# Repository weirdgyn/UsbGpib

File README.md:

# Table of contents

:newspaper: [Latest updates](Updates.md)
<br> :hammer: [Buy it or build it](#buy-it-or-build-it)
<br> :wave: [UsbGpib Introduction](#usbgpib-introduction)
<br> :house: [Housing / Enclosure](#housings)
<br> :computer: [Software](#software)
<br> &nbsp; &nbsp; :electric_plug: [Using the device](#using-the-device)
<br> &nbsp; &nbsp; :gear: [Setting and getting parameters](#setting-parameters)
<br> :heavy_check_mark: [Testing status](#testing-status)
<br> :notebook: [Tutorials](Tutorials/README.md) <- **New!**
<br> :heart: [Support the Project](#support-the-project)

# Summarized latest updates

For detailed visibility look under the Latest update link above!

[17h Aug 2026] Nice project: **[XyphroLabs-USBGpib-DMM4050](https://github.com/ZandanKhan/XyphroLabs-USBGpib-DMM4050)** — a Python GUI by [Zandan Khan](https://github.com/ZandanKhan) for controlling the Tektronix DMM 4050 (6½-digit precision multimeter) over UsbGpib, with measurement logging to CSV. Great example of building a full front-end on top of this adapter.

[17th Aug 2026]: **GPIBee is available, but...**

# GPIBee = UsbGpib V3 is available!

The title says it: GPIBee - UsbGpib V3 - is now available. Finally!  
  
It's for everyone who's told me, in issues and DMs, "I love this, but I don't have time to build one": USB-C and Ethernet with PoE, VXI-11 with multiple simultaneous sessions, and 3.5-5x the speed of V2 - in a proper enclosure, with real support behind it. 
It's built, tested, and shipping now.

I put together a short video showing it in action: [Introducing GPIBee](https://lnkd.in/epR7Xf-b).  
And you can find the full details at [GPIBee.com](https://www.gpibee.com).

This didn't come out of nowhere - there's a bit of a story behind it, including one thing I haven't said outright until now, something I went back and forth on for quite a while before deciding.

~7 years ago I started UsbGpib as a weekend project: An open, MIT-licensed way to talk to GPIB instruments without paying for an $800+ commercial adapter. I never expected it to pick up 642 stars, 82 forks, and end up soldered into home labs, universities, and repair benches around the world. That still means a lot to me, and it's the reason I kept and keep maintaining it for as long as I have.

A fair bit of that maintenance happened on evenings and weekends that would otherwise have gone to family time or just switching off. Nothing dramatic - just the normal trade-off of a side project that grew bigger than expected. Honestly, the part I'll remember most isn't the hours, it's the people: The issues, the emails, the odd late-night message or calls from someone debugging their own build. I've genuinely enjoyed those conversations, and they're a big part of why I kept going.

Along the way I also learned some harder lessons. To be clear, I've always been and are genuinely happy to see people or companies build their own UsbGpib - that's exactly what open source is for. What sat less well with me was seeing unrelated manufacturers turn V2 into a business of their own, selling it at scale with no attribution back to the project. That's a different thing entirely from working with official partners like Elecrow and Binho, who I have a real relationship with and who've supported this project properly.

But it stayed with me while I was figuring out what V3 should be, and it wasn't an easy decision to make.

So here's the thing I haven't said outright until now: V3 - GPIBee - is a commercial product rather than an open one. Something which might change in future, but for now it is.

That's a real change from V1/V2, and I don't want to gloss over it.

Here's the honest reasoning:

- Going commercial means there's a sustainable way to keep this going, rather than relying on whatever spare evenings I happen to have.
- It lets me fund the things a hobby project can't - CNC-machined, EMI-shielded enclosures, firmware QA, and proper support.
- It gives the project a legitimate path forward that undercutting clones can't quietly erase.

None of that changes what's already yours. V1 and V2 stay exactly as they are - MIT-licensed, fully open, schematics and firmware included, free to build and modify. And to be clear: I'm not walking away from it. I'll keep maintaining UsbGpib - answering issues, keeping it working - alongside GPIBee, not instead of it.

I'm proud of where this landed, and I'm looking forward to keeping both projects going - UsbGpib and GPIBee side by side. Thanks for seven years of bug reports and good conversations so far, with plenty more to come I hope. I hope some of you will give GPIBee a look, and either way, I'd genuinely love to hear what you think.

---

# Buy it or build it

* Tired of tinkering? Want to skip the hassle and get straight to using your GPIB setup?  
* You’d rather spend your time using your instruments instead of assembling hardware?

Skip the soldering iron and jump straight into your GPIB workflow!

You’ve got two solid options to get a ready‑to‑run UsbGpib adapter.

## &#x1f1fa;&#x1f1f8; - United States
* If you're in the US, you can now order the UsbGpibV2 directly from several sources, including my distribution partner Binho LLC. Enjoy fast domestic shipping with no long waits, no customs paperwork, and no surprises - just quick delivery and a smooth experience: 
<br> &#x1F449; <a href="https://binho.io/test-measurement/products/usbgpib-v2/" target="_blank">https://binho.io/test-measurement/products/usbgpib-v2/</a>
<br> &#x1F449; <a href="https://www.digikey.com/short/29nqq5cz" target="_blank"> https://www.digikey.com/short/29nqq5cz</a>
<br> &#x1F449; Amazon US also has it listed, but right now no stock, but worthwhile to check it out there too.

## &#x1F30E; - Worldwide
* I’ve teamed up with Elecrow to bring you ready-to-roll GPIB-USB converters – perfect for those who want results, not a weekend project.
* These adapters come fully assembled, programmed, housed, tested, and ready to go. No fuss. No build. Just plug it in and start working.
* The Adapters match 100% the V2 version described in this repository. 
* &#x1F449; <a href="https://www.elecrow.com/xyphrolabs-gpibusb.html" target="_blank">https://www.elecrow.com/xyphrolabs-gpibusb.html</a>

Let the data flow begin!

This doesn’t mean I’m going fully commercial - far from it.
Offering pre-built adapters is simply a convenience for those who’d rather skip the build and get straight to using their gear.

All sharing, support, and collaboration will remain fully open, just as before.
This is about choice, not change!

The full design files are located in this repository in case you want to build the devices yourself.

---

# UsbGpib Introduction
Versatile, cheap, portable and robust USB to GPIB converter (USBTMC class based).

You'll find many projects like this, but this one is special (ok, everybody will claim this) :-)

V1 Hardware: 

V2 Hardware: 

If you have a lot of test equipment at home, you might know the issues: Lots of devices only have GPIB as interface and the GPIB adapters and GPIB cables on the market are very expensive and some of them even have many issues, when run under Windows 10 (device driver does not work). Or they e.g. are not able to be operated with VISA, because they are UART based, need special command sequences, ...

The adapters are also typically very long, such that they extend the overall length of your test equipment by at least 10cm (~4 inches).

Apart of the 2 very big manufacturers, other GPIB adapters, e.g. with Ethernet or also USB interface are not recognized by normal VISA providers or PyVisa, making the measurement control implementation specific for your GPIB adapter.

I've got frustrated and tried to turn it into something positive. Here a video showing the final device in action - click to view:

Some goals of the project were:
- Work based on the standard USBTMC protocol. This allows the GPIB test equipment to look like a normal USB based measurement device and work flawless with e.g. NI VISA, Labview, Matlab or PyVisa.
- Have a small length - otherwise my equipment has the risk of falling from the shelf :-) Also the USB cable should connect 90 degree angled, to make it very short. With V2 HW, the length got further reduced to the size of a GPIB connector.
- It should be cheap but still versatile (you can build a single one of these for only 14 USD!)
- It should support ALL my test equipment, from many different GPIB implementation generations and different GPIB flavors
- The Firmware should be upgradeable over USB
- It should be rock-solid (!) I don't want to end up in a very long measurement being interrupted because of a software issue of my USB GPIB converter.
- It should support additional features like serial poll, remote enabling/disabling
- If there is no GPIB device connected to the USBGpib converter, or the GPIB device is powered down, there should be no USB device visible on the PC.

All those goals are met.

---

# Hardware

## Microcontroller choice

Although I typically would prefer nowadays an ARM Cortex M0/3/4/7 controller, there is an issue with it. Available devices support only max. 3.3V supply voltages, such that there would be a requirement for a level-shifter towards the GPIB Bus.
GPIB is based on 5V (not exactly true, but a first iteration).

This limited the microcontroller choice to e.g. AVR or PIC controllers. Because of very good availability I ended up in ATMEGA32U4 controllers.
Apart of the device supporting 5V I/O voltages, it also does not require a regulator to be part of the application - it has an internal 3.3V regulator. This minimizes the full application schematic and BOM.

Apart from that, there is an excellent USB stack available [http://www.fourwalledcubicle.com/LUFA.php](http://www.fourwalledcubicle.com/LUFA.php).

The GPIB side of the schematic can be directly connected to the ATMega32U4 IO pins. The IO pins from the microcontroller side are only set to 2 different states: Tri-state (input) or output LOW, to talk over GPIB.

## Component sourcing

All components are easy to source, so I only specify the potential critical ones:

- 16 MHz Crystal: Farnell 2853867 - MCSJK-7E-16.00-8-30-100-B-30 
- REV 1 GPIB connector: Farnell 2421095 - NORCOMP 112-024-113R001. For REV 2 use a straight 24P male solder type connector e.g. from AliExpress.
- USB connector for V1 HW: Farnell 2668483 - Amphenol ICC 61729-1011BLF
- USB connector for V2 HW: Best is to look on AliExpress for 57 series 24P connector as a starting point.

## PCB

The PCB can be ordered at nearly any PCB pool production service (e.g. 10 PCBs for 2 USD + shipping). The gerber files are included in the "HW/Gerber files" subdirectory.

## Mounting the PCB & Flashing the firmware

The PCB is available in 2 revisions.
- [REV 1](HW/REV1/README.md) is the most popularly used right now due to age. It has a USB Type-B connector and an L-shaped housing visible on a few photos of this page.
- [REV 2](HW/REV2/README.md) has some improvements like being smaller, better fit and USB Type-C connector.
- A REV 3 is upcoming. It will be a major redesign with more speed, Ethernet and power over Ethernet support, but the same DNA: Standard protocols being used and ensure compatibility and stability!

Choose whatever you prefer. The software images, but also the external behavior is the same.

---

# Housings

## REV 1

I created a sophisticated 3D printable housing for this adapter. The design was made with Fusion 360. The project file + the STL files are included in the "Housing" sub directory.

The PCB fits perfectly into it. Optionally it can be fixed with 2 mounting screws (the GPIB connector has 2 threads, use 2 times 4-40 UNC x 3/8) and the TOP cover snaps onto the housing base.

I printed this using an Ender 5 3D printer with black PLA, 0.15mm layer height, 1mm wall thickness, no support.
Take care, that you rotate the TOP part of the housing by 180 degrees, so that the flat side is located on the printer bed.
Printing works fine, several iterations of the design were made to ensure good printability.
I printed so far 15 housings, without a single fail.

More information on this REV 1 can be found here: [REV 1](HW/REV1/README.md).
Note, that also the programming/build instructions moved to this location.

## REV 2

The REV 2 housing is a lot smaller, but requires 2 screws.
The housing is quite important to be able to connect and disconnect the board without breaking anything. It is key for mechanical stability of the adapter.
When operating the device without housing, take very well care when plugging in and out the board in case the GPIB connector has a very tight fit.

Information on how to build it can be found in the HW/REV 2 folder: [REV 2](HW/REV2/README.md).
Note, that also the programming/build instructions moved to this location.

---

# Software

## Source code

The source code of the Boot loader (slightly modified LUFA MassStorage Boot loader) and the main USBGPIB converter are located in the "SW" subdirectory.
At the time of publication LUFA 170418 release was used, with GCC as compiler.

Note: The Software is compatible with any HW revision in this repository. For REV 1 and REV 2 hardware you don't need different SW images.

## Binaries

For those, that just want to create their own device, I've included the binary output in the "SW/binaries" subdirectory.

---

# Using the device

## USB enumeration

You might be surprised initially, that the device does not show up in your device manager (or lsusb), when you connect only the USB side. This is a feature, not a bug (really!).
Only, if a GPIB device is connected, you can see the device on your PC too.

The reason behind the feature is simple: Instead of having a standard GPIB wiring, where you have a single GPIB controller and lots of GPIB devices interconnected, USBGPIB supports only a direct connection of the USBGPIB device to your measurement device. If you have like me e.g. 14 Instruments you don't want all to show up in the device manager, if the measurement device itself is powered down - you won't anyway be able to communicate with a powered down device.

When USB and the GPIB side is connected, the device enumerates. The USBGPIB device reads out the ID of the instrument and constructs a unique USB Serial number out of it. It is thus easily possible to assiate multiple connected USBGPIB devices with the measurement instrument.

The VISA ressource name is constructed from this USB Serial number. You can identify easily e.g. in NiMax, which device is connected:

If you connect your USBGPIB device afterwards to another GPIB measurement device, it will disconnect and connect with a new serial number string, matching the other GPIB device *IDN? response again.

## GPIB settings on your measurement device

GPIBUSB does probe all GPIB primary addresses (and secondary address 0) for presence of a GPIB Talker/listener. It is thus not required to set a specific GPIB address - GPIBUSB will find it itself.

The only importance setting on the measurement device is, that the GPIB interface is enabled, which is typically the case.

## LED indicator

The LED indicates different states:

LED blinking: The USBGPIB converter is connected to a measurement instrument, it is powered off or its GPIB port is disabled. In this state, the device is also not connected to USB and will not show up in the device manager or lsusb.
LED on: The device is connected to a measurement device and GPIB communication possible. It is also accessible over USB
LED off: The device is not connected over USB, or the PC powered off :-)

## Controlling GPIB devices

As this converter implements the standard USBTMC Test and measurement class, you can control your instrument from ANY of the normal VISA tools. I tried so far R&S VISA and NI Visa, using Python and Matlab to talk to the devices.

# Testing status

This project is actively maintained since more than 6 years and I personally consider it as very stable. It is proven by multiple users to operate on MacOSX, Linux and Windows and measurement equipment from several decades.

In general I take bug reports very serious and want to "fix them all". In case you don't get an answer on-time on items you report in the issues section, please write me: Xyphro@gmail.com. 
I often miss seeing issue reports very quickly, as I don't get an email once they are filed.

## Sucessfully tested measurement equipment:

Below list is equipment I mainly myself tested. Many other users have other measurement equipment proven in use already.

- R&S FSEM30
- R&S SMIQ03
- R&S CMU200
- R&S SMW200A
- R&S FSW
- R&S FSV
- Keithley 199 multimeter
- HP 34401 DMM from different generations / with different FW versions
- HP 3325A synthesizer/frequency generator
- HP 3457A multimeter
- Agilent E4406A VSA transmitter tester
- Tektronix TDS7104 Digital Phosphor Oscilloscope
- HP 8596A spectrum analyzer
- Agilent E3648A dual power supply

A rather incomplete summary of equipment reported to work from users is:
- Keithley S46T
- HP/Agilent/Keysight 34401A of different generations
- HP/Aglient/Keysight 34410A
- Agilent N6700B
- Agilent E4416A
- Agilent 34970
- Keysight E3645A
- Keithley 2230G-30-1
- Keithley 2601A
- Tektronix AFG3102
- Tektronix 3014C
- Rohde & Schwarz SMB 100A
- Agilent E3631A
- ICS 4899GPIB
- TTI QL564TP
- Lecroy LW110
- LeCroy 334A
- LeCroy 354A
- Hameg 3524
- Fluke 5522A
- Fluke 5500A 
- and many more... It will take quite a while till I have parsed all my emails for working instruments :-)

## Scenarious

- It works under all popular operating systems like Windows 7 and 10, 11, Linux and MacOSX
- USB1.1, USB2.0 and USB3.x ports tested, with and without USB HUB in between.
- The connection stays responsive, when power cycling the PC, or hibernating/sleeping it
- Different connection cycles (GPIB side connected first, USB side connected first, swapping GPIB side equipment, ...)
- Extensive testing of timeout scenarious. E.g. making an illegal query and testing, if the USBTMC handles the timeouts properly. This was a very tricky part to get right.
- Tested special transfer modes. E.g. capturing screenshots from different equipment is usually something, which will drive other GPIB adapters to the limits, because binary data of unknown length needs to be transported successfully.

# Setting Parameters

The firmware version from 13th January 2024 onwards has the ability for human readable text base configuration of several parameters.
The previous methods are still supported, but won't be further documented. You can look them back in the history of this file.

The command parser is quite simple. For that reason follow the exact syntax as shown below. 
Don't add extra spaces or make other modifications or concatenate commands.

## Read termination method

While most GPIB interfaces use the hardware signal EOI to signal the end of a message, not all old equipment supports it. Some older instruments even don't have the EOI pin hardware wise wired and use \r or \n termination.

The USB-TMC standard allows to set the read termination. While in firmware versions before < 2.0 I did not enable that method, it is now finally supported with standard compliance.

I document here the older method (using pulse indicator request), but I add also the newer methods which are 100% UsbTmc compliant and portable across different equipments. You can choose which ones to use, but in some cases pulse indicator requests can be difficult to issue, for which reason it is likely better to use the standard compliant method.

### Set read termination to CR (\r):
(old method)
```
dev.control_in(0xa1, 0x40, 0, 0, 1); # USBTMC pulse indicator request (enables internal command processing)
dev.write('!term cr')
```
Above setting is volatile. To make this a permanent setting call the below mentioned "!term store" command.

(prefered method) Alternatively you can set the termination directly with visa means, e.g. using PyVisa:
```
dev.set_visa_attribute(visa.constants.VI_ATTR_TERMCHAR_EN, True)
dev.set_visa_attribute(visa.constants.VI_ATTR_TERMCHAR, ord('\r') )
```

### Set read termination to LF (\n):
(old method)
```
dev.control_in(0xa1, 0x40, 0, 0, 1); # USBTMC pulse indicator request (enables internal command processing)
dev.write('!term lf')
```
Above setting is volatile. To make this a permanent setting call the below mentioned "!term store" command.

(prefered method) Alternatively you can set the termination directly with visa means, e.g. using PyVisa:
```
dev.set_visa_attribute(visa.constants.VI_ATTR_TERMCHAR_EN, True)
dev.set_visa_attribute(visa.constants.VI_ATTR_TERMCHAR, ord('\n') )
```

### Set read termination to EOI only (default setting):
(old method) 
```
dev.control_in(0xa1, 0x40, 0, 0, 1); # USBTMC pulse indicator request (enables internal command processing)
dev.write('!term eoi')
```
Above setting is volatile. To make this a permanent setting call the below mentioned "!term store" command.

(prefered method) Alternatively you can set the termination directly with visa means, e.g. using PyVisa:
```
dev.set_visa_attribute(visa.constants.VI_ATTR_TERMCHAR_EN, False)
dev.set_visa_attribute(visa.constants.VI_ATTR_TERMCHAR, ord('\0') )
```

### Save readtermination setting in eeprom (make them non-volatile)
```
dev.control_in(0xa1, 0x40, 0, 0, 1); # USBTMC pulse indicator request (enables internal command processing)
dev.write('!term store')
```

Above relates to the "old non prefered method". In general it is a good idea to set the read termination volatile and use the above suggested methods highlighted with (prefered method).

### Query current termination setting from device
```
dev.control_in(0xa1, 0x40, 0, 0, 1); # USBTMC pulse indicator request (enables internal command processing)
print(dev.query('!term?'))
```
This returns a text string containing "lf", "cr" or "eoi"

## Multi-device support - Setting the GPIB device target address

Since Firmware version V2.4 USBGpib allows supporting multiple instruments.

While the USBTMC protocol allows only setting a single device to be addressed and composite USB devices are not well supported by all VISA implementations, I decided to add a command to set the address of the GPIB device which is addressed.

There is a minor limitation of this approach, which is that service request SRQ handling is only done properly to the currently selected GPIB device.
Another one is, that users shall never forget to set the GPIB address to the correct setting before issuing a command.

### Setting a primary address only

Substitute the text <Primary_address> with a number from 1 to 30 to set the primary address of the new GPIB device to talk to in following GPIB transactions

```
dev.control_in(0xa1, 0x40, 0, 0, 1);
dev.write('!addr <Primary_address>')
```

### Setting a primary + secondary address

Substitute the text <Primary_address> with a number from 1 to 30 to set the primary address and <Secondary_address> with a number from 0..6 or 96..102 of the new GPIB device to talk to in following GPIB transactions.
Note, that not the full subaddress range of 0..31 or 96..127 is supported as of now - this requires a bit more work. Most common device with subaddresses like R&S CMU200 only are well covered with that current range.

```
dev.control_in(0xa1, 0x40, 0, 0, 1);
dev.write('!addr <Primary_address> <Secondary_address>')
```
### Python wrapper example code for GPIB address setting

```
import pyvisa as visa
dev = 'USB0::0x03EB::0x2065::GPIB_22_14236333938351C00011::INSTR'
rm = visa.ResourceManager()
dev = rm.open_resource(dev, open_timeout=1000)

def set_gpib_addr(primary_address, secondary_address = None):
    dev.control_in(0xa1, 0x40, 0, 0, 1);
    if secondary_address is None:
        dev.write('!addr %d' % primary_address);
    else:
        dev.write('!addr %d %d' % (primary_address, secondary_address));
    
# Address CMU200, which is for me on primary address 1, secondary address 0
set_gpib_addr(1, 0)
print(dev.query('*IDN?'))

# address HP3457A on primary GPIB address 22
set_gpib_addr(22)
dev.write('END,ALWAYS')
print(dev.query('ID?'))
```

This code results in my current testsetup with CMU200 and HP3457A in this output:

```
Rohde&Schwarz,CMU 200-1100.0008.02,xxxxxx,V5.22

HP3457A
```

## AutoID setting

Default wise the GPIB adapter tries during power on of the instrument to query using *IDN? or ID? commands the instrument name automatically.
This is used to build the USB serial number, which finally gets part of the VISA ressource string.

Not all instruments support this *IDN / ID? query. For this reason this feature can be turned off.
The serial number will then be built based on the GPIB address of the instrument.

### Turn AutoID feature off
```
dev.control_in(0xa1, 0x40, 0, 0, 1); # USBTMC pulse indicator request (enables internal command processing)
dev.write('!autoid off')
```
This setting is stored in eeprom = non volatile memory, so will survive a power cycle

### Turn AutoID feature on
```
dev.control_in(0xa1, 0x40, 0, 0, 1); # USBTMC pulse indicator request (enables internal command processing)
dev.write('!autoid on')
```
This setting is stored in eeprom = non volatile memory, so will survive a power cycle

### turn auto ID on with delay

Some instruments need after turn on some seconds before GPIB is responsive.

With below 3 settings you can set a delay which is applied before the instrument ID is queried after power on.
Note that it will take then also more time, before the USB device is recognized by the PC.

Also this setting is non-volatile.

Delay 5 seconds:
```
dev.control_in(0xa1, 0x40, 0, 0, 1); # USBTMC pulse indicator request (enables internal command processing)
dev.write('!autoid slow')
```

Delay 15 seconds:
```
dev.control_in(0xa1, 0x40, 0, 0, 1); # USBTMC pulse indicator request (enables internal command processing)
dev.write('!autoid slower')
```

Delay 30 seconds:
```
dev.control_in(0xa1, 0x40, 0, 0, 1); # USBTMC pulse indicator request (enables internal command processing)
dev.write('!autoid slowest')
```

### read autoid setting

```
dev.control_in(0xa1, 0x40, 0, 0, 1); # 
print(dev.query('!autoid?'))
```
Returns as text string either: "off", "on", "slow", "slower" or "slowest".

## Firmware version

Finally I implemented a command to query the USB adapters firmware version :-)

```
dev.control_in(0xa1, 0x40, 0, 0, 1); # USBTMC pulse indicator request (enables internal command processing)
print(dev.query('!ver?'))
```

## Shorten ressource strings (Matlab)

A user discovered that Matlab has a limitation in the VISA ressource string length and shared a pull request to reduce the length.
I expose this now first time in the baseline firmware with the following options.

This setting is stored in eeprom = non volatile.

### Limit the USB serial number to a length of 20 characters
```
dev.control_in(0xa1, 0x40, 0, 0, 1); # USBTMC pulse indicator request (enables internal command processing)
dev.write('!string short')
```

### disable limitation of USB serial number length (default behavior)
```
dev.control_in(0xa1, 0x40, 0, 0, 1); # USBTMC pulse indicator request (enables internal command processing)
dev.write('!string normal')
```

### query the string length setting.
```
dev.control_in(0xa1, 0x40, 0, 0, 1); # USBTMC pulse indicator request (enables internal command processing)
print(dev.query('!string?'))
```

This returns as text string either "normal" or "short".

## reset the adapter
```
dev.control_in(0xa1, 0x40, 0, 0, 1); 
dev.write('!reset')
```

Do a reset of the adapter. Note that due to the reset you have to close the visa session and start a new one as the device re-enumerates on the USB.

---

# Support the project

Or support by buying a fully prebuilt adapter at: <a href="https://www.elecrow.com/xyphrolabs-gpibusb.html" target="_blank">https://www.elecrow.com/xyphrolabs-gpibusb.html</a>

In general any email, post or feedback is also very valuable, and don't feel bad if you don't use the support options :-)
Feel free to contact me at Xyphro@gmail.com

---

This page is from XyphroLabs UsbGpib project: <a href="https://github.com/xyphro/UsbGpib" target="_blank">https://github.com/xyphro/UsbGpib</a>

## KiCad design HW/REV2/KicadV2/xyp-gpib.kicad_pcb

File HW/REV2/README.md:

# xyphro UsbGpib HW REV 2

The new HW revision picks up some things that I and other misliked:
- The REV 1 HW - when put beeing assembled into its housing did have change to colide with parts of the instruments body. Especially for Keysight equipment. This new HW revision follows the formfactor of an original GPIB cable to get rid of this mechanical constraint.
- The REV 1 HW required to enter the bootloader with a tweezer. REV 2 has a button. Hold it a few seconds and the bootloader is entered.

The [software](../../SW) will always stay the same, no matter if REV1 or REV 2.

I have built many of those adapters myself so far and have developed trust in the design:

## Assembly process

All files related to HW are located in this folder. Gerber file, BOM, Kicad design files.

## preparing the PCB

Mount only the SMD components. This means: DON'T mount the GPIB connector yet.

On edge you can find a mounting point for a pinheader - 45 degrees angled. Mount 2-3 pin pinheaders here and you now have a 6 pin ISP programming port with standard pinout for your favorit AVR programmer.
Program the bootloader. Pin 1 is marked on the PCB to allow you connecting the ISP cable in the correct orientation.

### Flashing the Microcontroller first time

For initial programming an AVR ISP adapter is needed to program the "Bootloader.hex" file.

It is very important, that the Fuses of the AVR are programmed.

Here an example how to program the bootloader using avrdude (using usbasp programmer):
```
avrdude -c usbasp -p m32u4 -e -Ulock:w:0xFF:m -Uefuse:w:0xcb:m -Uhfuse:w:0xd8:m -Ulfuse:w:0xde:m
avrdude -c usbasp -p m32u4 -U flash:w:BootLoader.hex
```
To program bootloader and application image at the same time using AvrDude, you can use this command:
```
avrdude -c usbasp -p m32u4 -e -Ulock:w:0x3F:m -Uefuse:w:0xcb:m -Uhfuse:w:0xd8:m -Ulfuse:w:0xde:m -U flash:w:TestAndMeasurement.hex -U flash:w:BootLoader.hex
```
Note, that some programmers use a quite high clock frequency on the programming interface. In case of failures try to decrease the SCK clock frequency!

After programming the file, disconnect and connect the device and a USB drive will show up. Copy the TestAndMeasurement.bin file to this USB drive - ideally using the command line. Example: `copy TestAndMeasurement.bin F:\FLASH.BIN`.
On Linux, there is a bug with the LUFA mass storage that means it is required to use `dd if=TestAndMeasurement.bin of=/mnt/FLASH.BIN bs=512 conv=notrunc oflag=direct,sync`.

When done, disconnect USB.

It is now safe to desolder the ISP pinheaders such that the PCB fits into the housing. 
Any further update can happen over USB using the bootloader.

## Building the whole thing together
Preparation:
- Mount the PCB EXCLUDING the GPIB connector.
- Print the housings located in [this folder](../../Housing/Rev2). I print them using 1mm bottom/top/wall thickness, 0.16mm layer height and 30% infil. On my K1 printer it takes 23 minutes to print, on my Ender 5 2.2 hours.
- get 2 20mm M3 screws and 2 M3 nuts
- get a GPIB connector "24P Male solder type" from e.g. Aliexpress

If you have everything in place and prepared, insert the PCB including the GPIB connector (unsoldered!) into the bigger part of the housing:

Then solder 2 pins of the GPIB connector and take the PCB out of the housing again to solder all pins.
(This step is required to ensure that the GPIB connector has the right distance to the PCB and fit into the housing)

As a next step insert the PCB into the big part of the housing again. It has a relatively tight fit - to ensure mechanic stability.

Then put the smaller part of the housing on top of it, insert the screws (they can be pushed hard to destroy the "membrane" first time) and nuts and screw it together.

Voilà... your adapter is finished and ready to use :-)

# Updating the firmware at later stages

To enter the boot loader at later stages for updates, press the button (bigger hole in the housing) using a pen/paperclip for about 3 seconds. Then a USB mass storage (flash drive) enumerates on the PC where the firmware image can be copied too (see previous chapter).

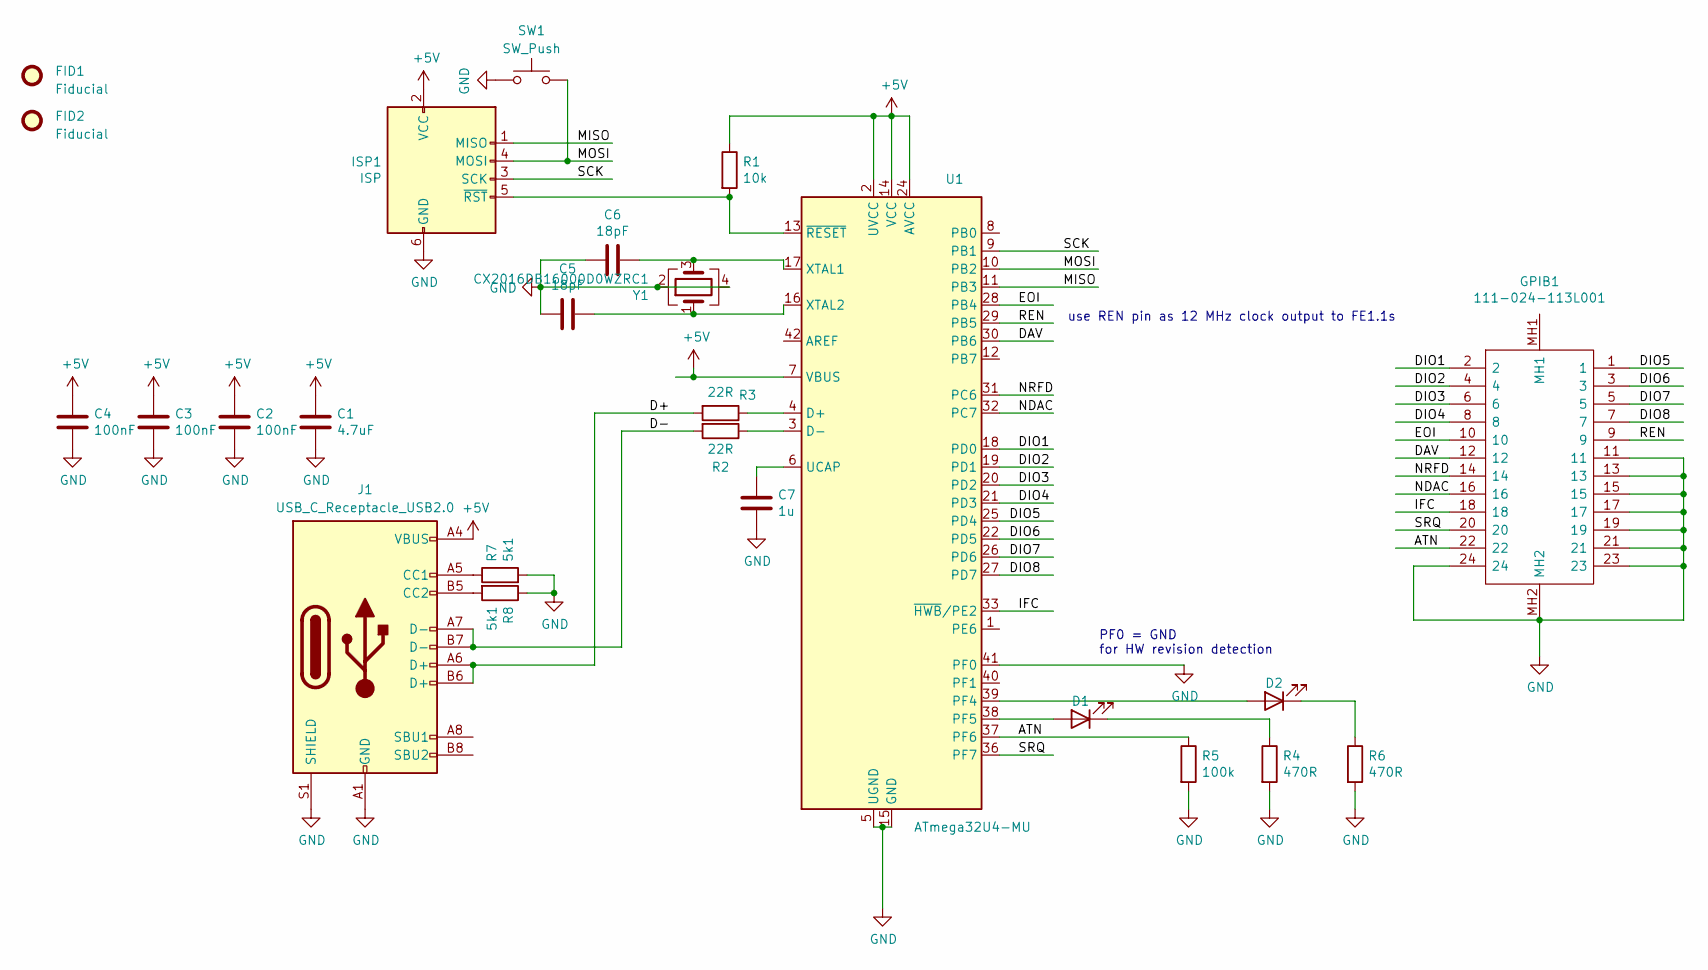
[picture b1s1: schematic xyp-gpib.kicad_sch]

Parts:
C1: 4.7uF; C_0805_2012Metric
C2, C3, C4: 100nF; C_0603_1608Metric
C5, C6: 18pF; C_0603_1608Metric
C7: 1u; C_0603_1608Metric
D1, D2: LED; LED_0805_2012Metric
FID1, FID2: Fiducial; Fiducial_0.5mm_Mask1mm
GPIB1: 111-024-113L001; 112024113R001; Manufacturer_Part_Number 112-024-113R001; Mouser Part Number 636-112-024-113R001
ISP1: ISP; EdgeProg
J1: USB_C_Receptacle_USB2.0; USB_C_Receptacle_XKB_U262-16XN-4BVC11
R1: 10k; R_0603_1608Metric
R2, R3: 22R; R_0603_1608Metric
R4, R6: 470R; R_0603_1608Metric
R5: 100k; R_0603_1608Metric
R7, R8: 5k1; R_0603_1608Metric
SW1: SW_Push; SW_Tactile_SPST_NO_Straight_CK_PTS636Sx25SMTRLFS
U1: ATmega32U4-MU; QFN-44-1EP_7x7mm_P0.5mm_EP5.2x5.2mm
Y1: CX2016DB16000D0WZRC1; Crystal_SMD_2016-4Pin_2.0x1.6mm

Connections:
+5V: C1.1, C2.1, C3.1, C4.1, ISP1.2 (VCC), J1.A4 (VBUS), J1.A9 (VBUS), J1.B4 (VBUS), J1.B9 (VBUS), R1.1, U1.2 (UVCC), U1.7 (VBUS), U1.14 (VCC), U1.24 (AVCC), U1.34 (VCC), U1.44 (AVCC)
/ATN: GPIB1.22, R5.1, U1.37 (PF6)
/D+: J1.A6 (D+), J1.B6 (D+), R3.2
/D-: J1.A7 (D-), J1.B7 (D-), R2.2
/DAV: GPIB1.12, U1.30 (PB6)
/DIO1: GPIB1.2, U1.18 (PD0)
/DIO2: GPIB1.4, U1.19 (PD1)
/DIO3: GPIB1.6, U1.20 (PD2)
/DIO4: GPIB1.8, U1.21 (PD3)
/DIO5: GPIB1.1, U1.25 (PD4)
/DIO6: GPIB1.3, U1.22 (PD5)
/DIO7: GPIB1.5, U1.26 (PD6)
/DIO8: GPIB1.7, U1.27 (PD7)
/EOI: GPIB1.10, U1.28 (PB4)
/IFC: GPIB1.18, U1.33 (~HWB/PE2)
/MISO: ISP1.1 (MISO), U1.11 (PB3)
/MOSI: ISP1.4 (MOSI), SW1.2, U1.10 (PB2)
/NDAC: GPIB1.16, U1.32 (PC7)
/NRFD: GPIB1.14, U1.31 (PC6)
/REN: GPIB1.9, U1.29 (PB5)
/SCK: ISP1.3 (SCK), U1.9 (PB1)
/SRQ: GPIB1.20, U1.36 (PF7)
GND: C1.2, C2.2, C3.2, C4.2, C5.2, C6.2, C7.2, GPIB1.11, GPIB1.13, GPIB1.15, GPIB1.17, GPIB1.19, GPIB1.21, GPIB1.23, GPIB1.24, GPIB1.MH2, ISP1.6 (GND), J1.A1 (GND), J1.A12 (GND), J1.B1 (GND), J1.B12 (GND), J1.S1 (SHIELD), R4.2, R5.2, R6.2, R7.2, R8.1, SW1.1, U1.5 (UGND), U1.15 (GND), U1.23 (GND), U1.35 (GND), U1.41 (PF0), U1.43 (GND), U1.45 (GND), Y1.2, Y1.4
unnamed: D1.2 (A), U1.38 (PF5)
unnamed: D1.1 (K), R4.1
unnamed: D2.2 (A), U1.39 (PF4)
unnamed: D2.1 (K), R6.1
unnamed: ISP1.5 (~RST), R1.2, U1.13 (~RESET)
unnamed: J1.A5 (CC1), R7.1
unnamed: J1.B5 (CC2), R8.2
unnamed: R3.1, U1.4 (D+)
unnamed: R2.1, U1.3 (D-)
unnamed: C7.1, U1.6 (UCAP)
unnamed: C6.1, U1.17 (XTAL1), Y1.3
unnamed: C5.1, U1.16 (XTAL2), Y1.1

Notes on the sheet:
PF0 = GND for HW revision detection
use REN pin as 12 MHz clock output to FE1.1s

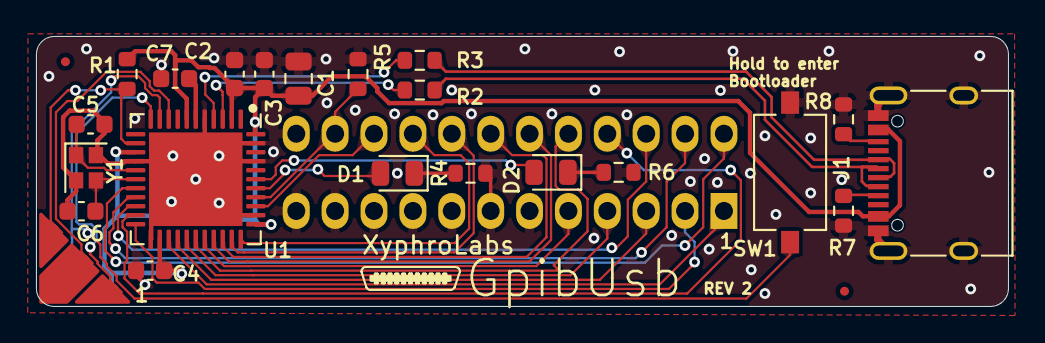
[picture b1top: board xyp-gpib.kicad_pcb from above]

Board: 2 copper layers, 54.0 x 15.0 mm, 25 parts (1 on the bottom side), 35 nets.

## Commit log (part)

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2026-06-09 update some notes in the user manual
2026-06-09 some updates
    - extended list of supported documents (I got MUCH MUCH more reported, but it is hard to find that all back in my email inbox)
    - Shared that KE5FX got ported by W6DVN to support UsbGpib V2
